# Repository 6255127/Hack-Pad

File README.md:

# Hackpad

A custom 3x4 macro keyboard I built from scratch - schematic, PCB, 3D printed case, and firmware, all done by me as a portfolio/hackathon project. Built around an Arduino Nano RP2040 Connect, with a rotary encoder, OLED status screen, and per-key RGB backlighting.

## Features
- 3x4 key matrix (12 keys)
- rotary encoder for scroll/navigation
- 0.91" OLED showing current layer, last key pressed, and time (synced over wifi)
- SK6812 addressable LEDs under each key
- two layers - numpad mode and a shortcuts mode (copy/paste/undo/save/etc)
- wired usb keyboard (bluetooth planned later, board already supports it)

---

## 1. Schematic

Designed in KiCad. Went through a few pin conflicts along the way (accidentally put the LED data line on the I2C bus at one point) before landing on the final wiring.

---

## 2. PCB routing

Routed as a 2-layer board - rows on the bottom copper, columns on top, vias where they cross. Ran into a mixed-up switch numbering issue during routing that caused some real weird ratsnest jumps, fixed by re-checking every switch against the row/column table by hand.

---

## 3. 3D case

Modeled in Fusion 360 / Onshape, sandwich-mount style. Bottom half holds the PCB and MCU, top half is the switch plate with cutouts for keycaps, the encoder, and the OLED window. Top plate designed to be printed in clear/frosted material so the LEDs glow through it.

---

## 4. Firmware

Written in Arduino for the Nano RP2040 Connect. Handles matrix scanning, encoder input, LED feedback, OLED display, and layer switching (numpad vs shortcuts) via the encoder click.

---

## To-do
- bluetooth (board already has the chip, just needs the firmware side)
- battery + charging circuit
- silkscreen art on the back

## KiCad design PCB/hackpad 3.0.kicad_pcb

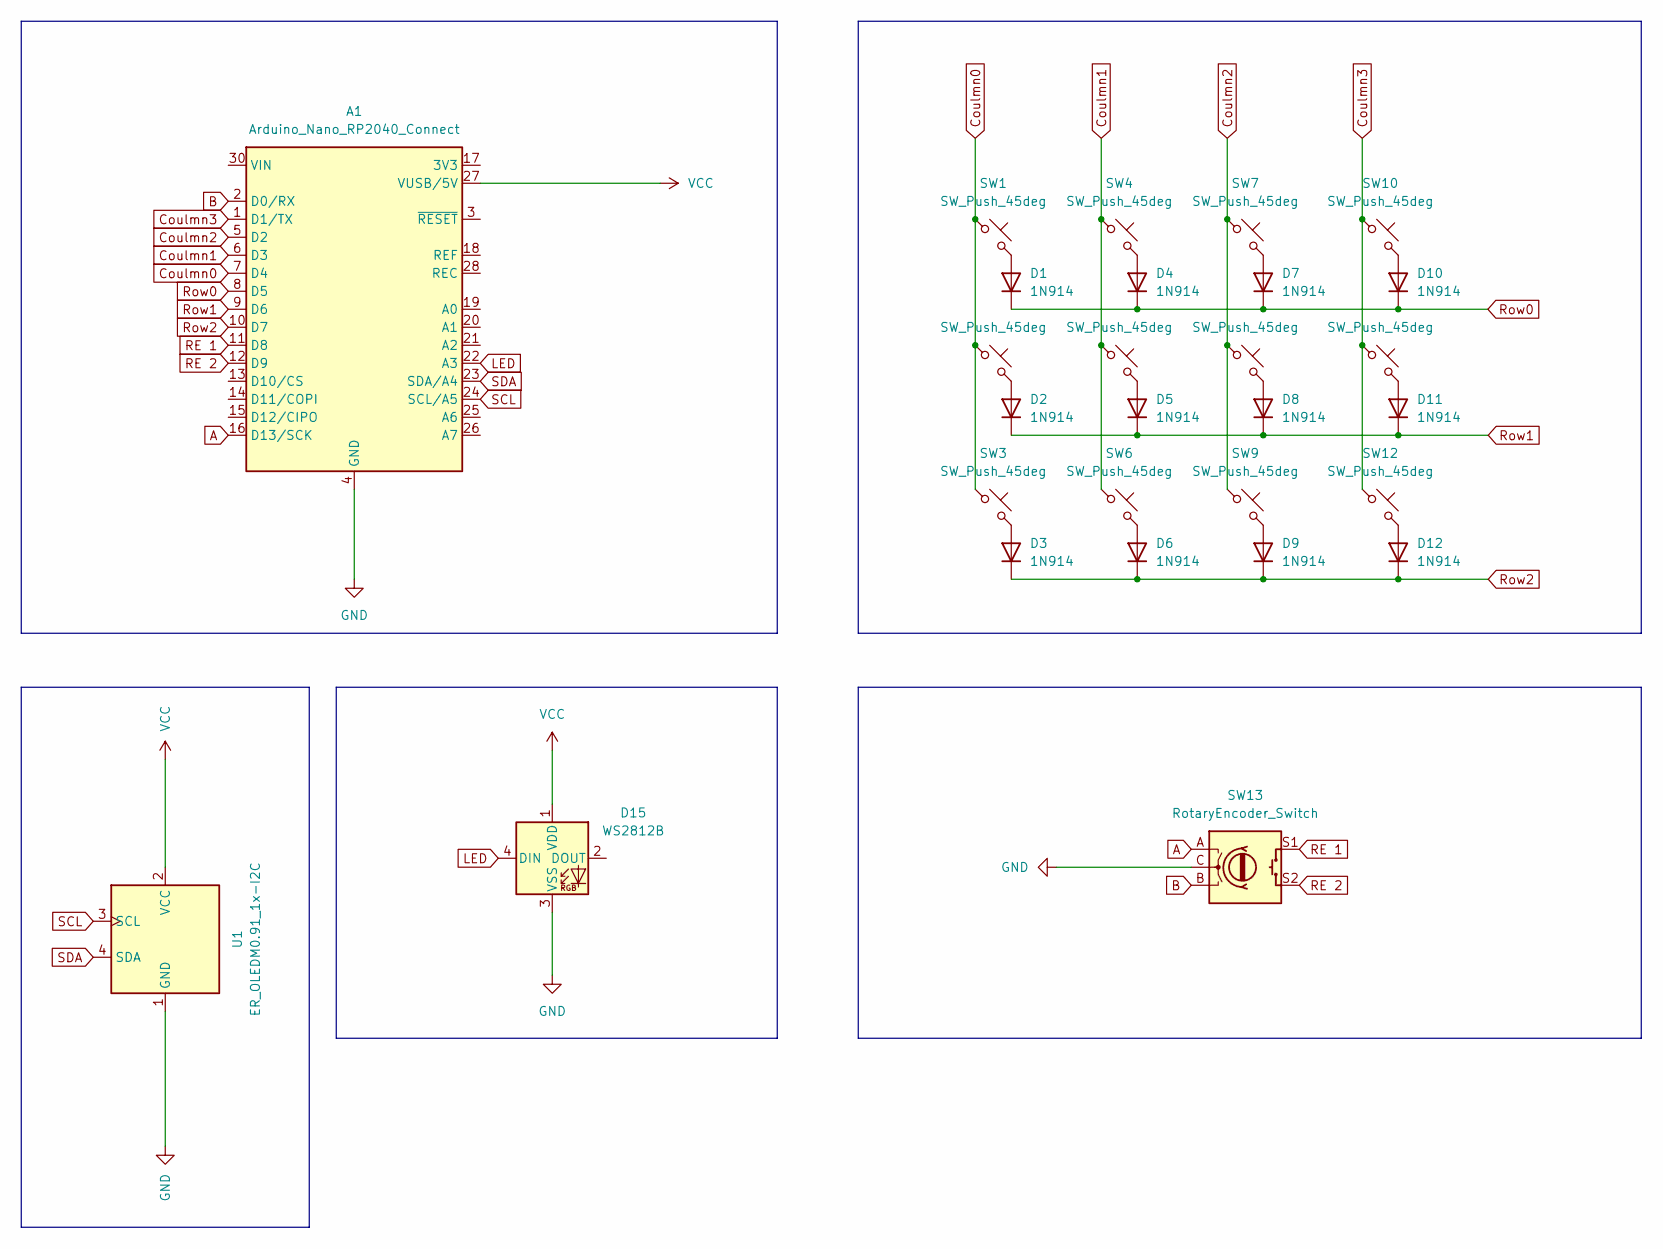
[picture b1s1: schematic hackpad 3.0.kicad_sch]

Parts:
A1: Arduino_Nano_RP2040_Connect; Arduino_Nano_WithMountingHoles
D1, D2, D3, D4, D5, D6, D7, D8, D9, D10, D11, D12: 1N914; D_DO-35_SOD27_P7.62mm_Horizontal
D15: WS2812B; LED_WS2812B-Mini_PLCC4_3.5x3.5mm
SW1, SW2, SW3, SW4, SW5, SW6, SW7, SW8, SW9, SW10, SW11, SW12: SW_Push_45deg; SW_Cherry_MX_1.00u_PCB
SW13: RotaryEncoder_Switch; RotaryEncoder_Alps_EC11E-Switch_Vertical_H20mm
U1: ER_OLEDM0.91_1x-I2C

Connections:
A: A1.16 (D13/SCK), SW13.A
B: A1.2 (D0/RX), SW13.B
Coulmn0: A1.7 (D4), SW1.1, SW2.1, SW3.1
Coulmn1: A1.6 (D3), SW4.1, SW5.1, SW6.1
Coulmn2: A1.5 (D2), SW7.1, SW8.1, SW9.1
Coulmn3: A1.1 (D1/TX), SW10.1, SW11.1, SW12.1
GND: A1.4 (GND), A1.29 (GND), D15.3 (VSS), SW13.C, U1.1 (GND)
LED: A1.22 (A3), D15.4 (DIN)
unnamed: D1.2 (A), SW1.2
unnamed: D2.2 (A), SW2.2
unnamed: D3.2 (A), SW3.2
unnamed: D4.2 (A), SW4.2
unnamed: D5.2 (A), SW5.2
unnamed: D6.2 (A), SW6.2
unnamed: D7.2 (A), SW7.2
unnamed: D8.2 (A), SW8.2
unnamed: D9.2 (A), SW9.2
unnamed: D10.2 (A), SW10.2
unnamed: D11.2 (A), SW11.2
unnamed: D12.2 (A), SW12.2
RE 1: A1.11 (D8), SW13.S1
RE 2: A1.12 (D9), SW13.S2
Row0: A1.8 (D5), D1.1 (K), D4.1 (K), D7.1 (K), D10.1 (K)
Row1: A1.9 (D6), D2.1 (K), D5.1 (K), D8.1 (K), D11.1 (K)
Row2: A1.10 (D7), D3.1 (K), D6.1 (K), D9.1 (K), D12.1 (K)
SCL: A1.24 (SCL/A5), U1.3 (SCL)
SDA: A1.23 (SDA/A4), U1.4 (SDA)
VCC: A1.27 (VUSB/5V), D15.1 (VDD), U1.2 (VCC)

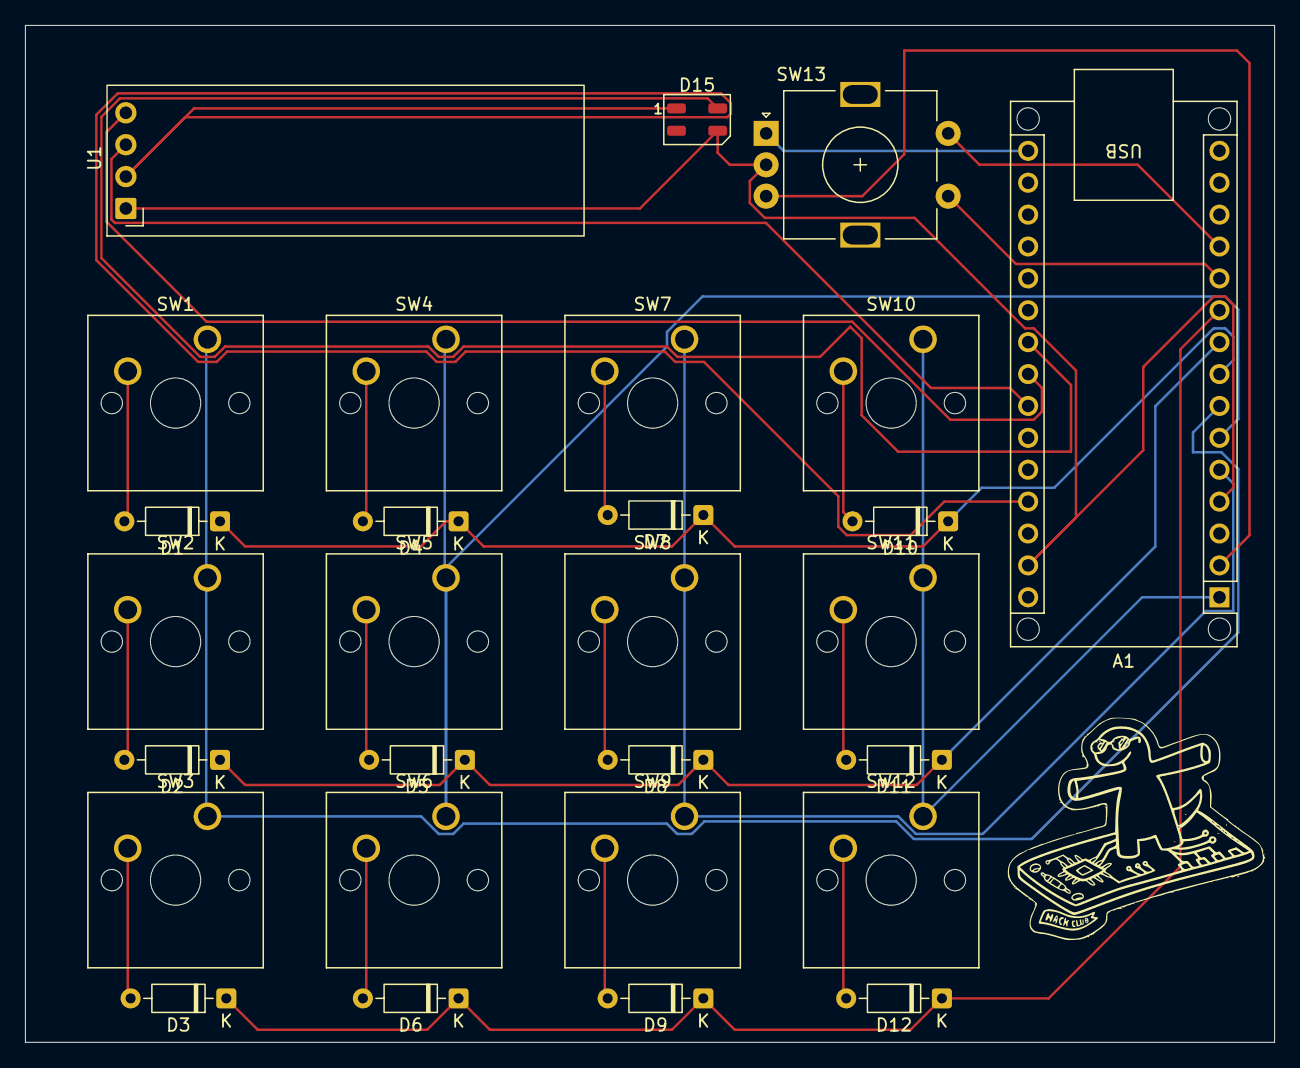
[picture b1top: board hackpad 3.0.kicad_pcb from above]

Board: 2 copper layers, 99.5 x 81.0 mm, 28 parts (0 on the bottom side), 28 nets.

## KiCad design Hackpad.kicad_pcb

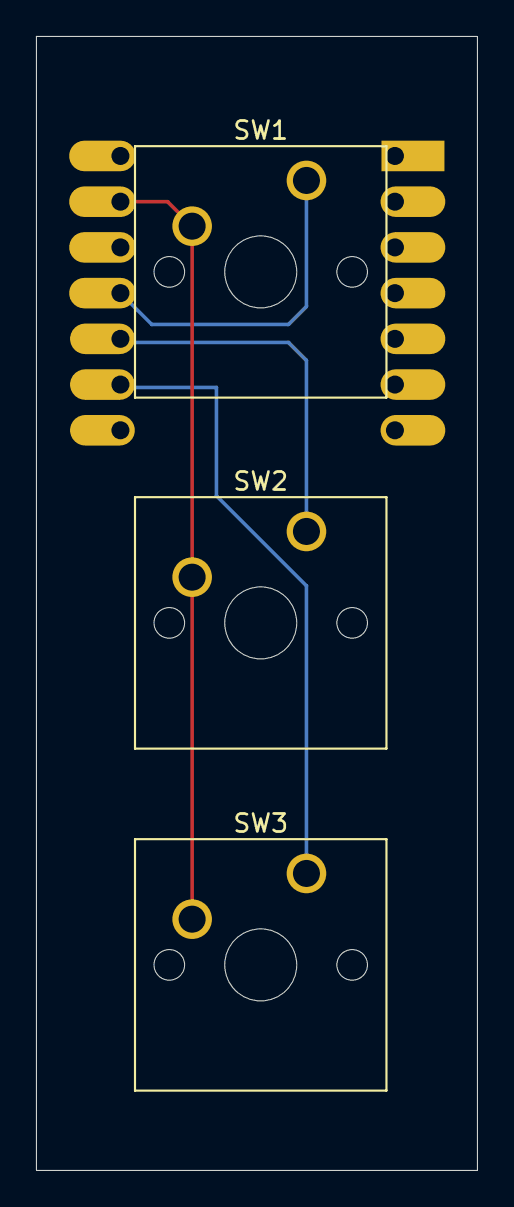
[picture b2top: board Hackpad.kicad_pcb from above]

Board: 2 copper layers, 24.5 x 63.0 mm, 4 parts (1 on the bottom side), 4 nets.

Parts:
SW1, SW2, SW3: SW_Push; SW_Cherry_MX_1.00u_PCB
U1: MOUDLE-SEEEDUINO-XIAO; XIAO-Generic-Hybrid-14P-2.54-21X17.8MM

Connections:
GNDA: SW1.2, SW2.2, SW3.2, U1.13 (GND)
unnamed: SW2.1, U1.10 (PA5_A9_D9_MISO)
unnamed: SW1.1, U1.11 (PA6_A10_D10_MOSI)
unnamed: SW3.1, U1.9 (PA7_A8_D8_SCK)
